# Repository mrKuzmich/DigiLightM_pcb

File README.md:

# DigiLight-M
DigiLight-M is a project of digital light organ with automat of light effects. This project based on [DigiLight](https://cxem.net/sound/light/light127.php) project of user [AVR](https://cxem.net/profile/17379).

This part of the project contains the schematic of the device itself and PCB. The source codes of the ATMega32 microcontroller firmware in the C language you can see in another part of the project [DigiLightM_firmware](https://github.com/mrKuzmich/DigiLightM_firmware).

## Whats new
1. Changed the power suply of the digital and analog parts of circuit;
2. Added line-in and microphone input with electronic source selection;
3. SD Card adapter replaced with direct connection of MicroSD Card;
4. Redesigned PCB. 

## Appearance

## Schematic

## Firmware
[DigiLightM_firmware](https://github.com/mrKuzmich/DigiLightM_firmware) repository.

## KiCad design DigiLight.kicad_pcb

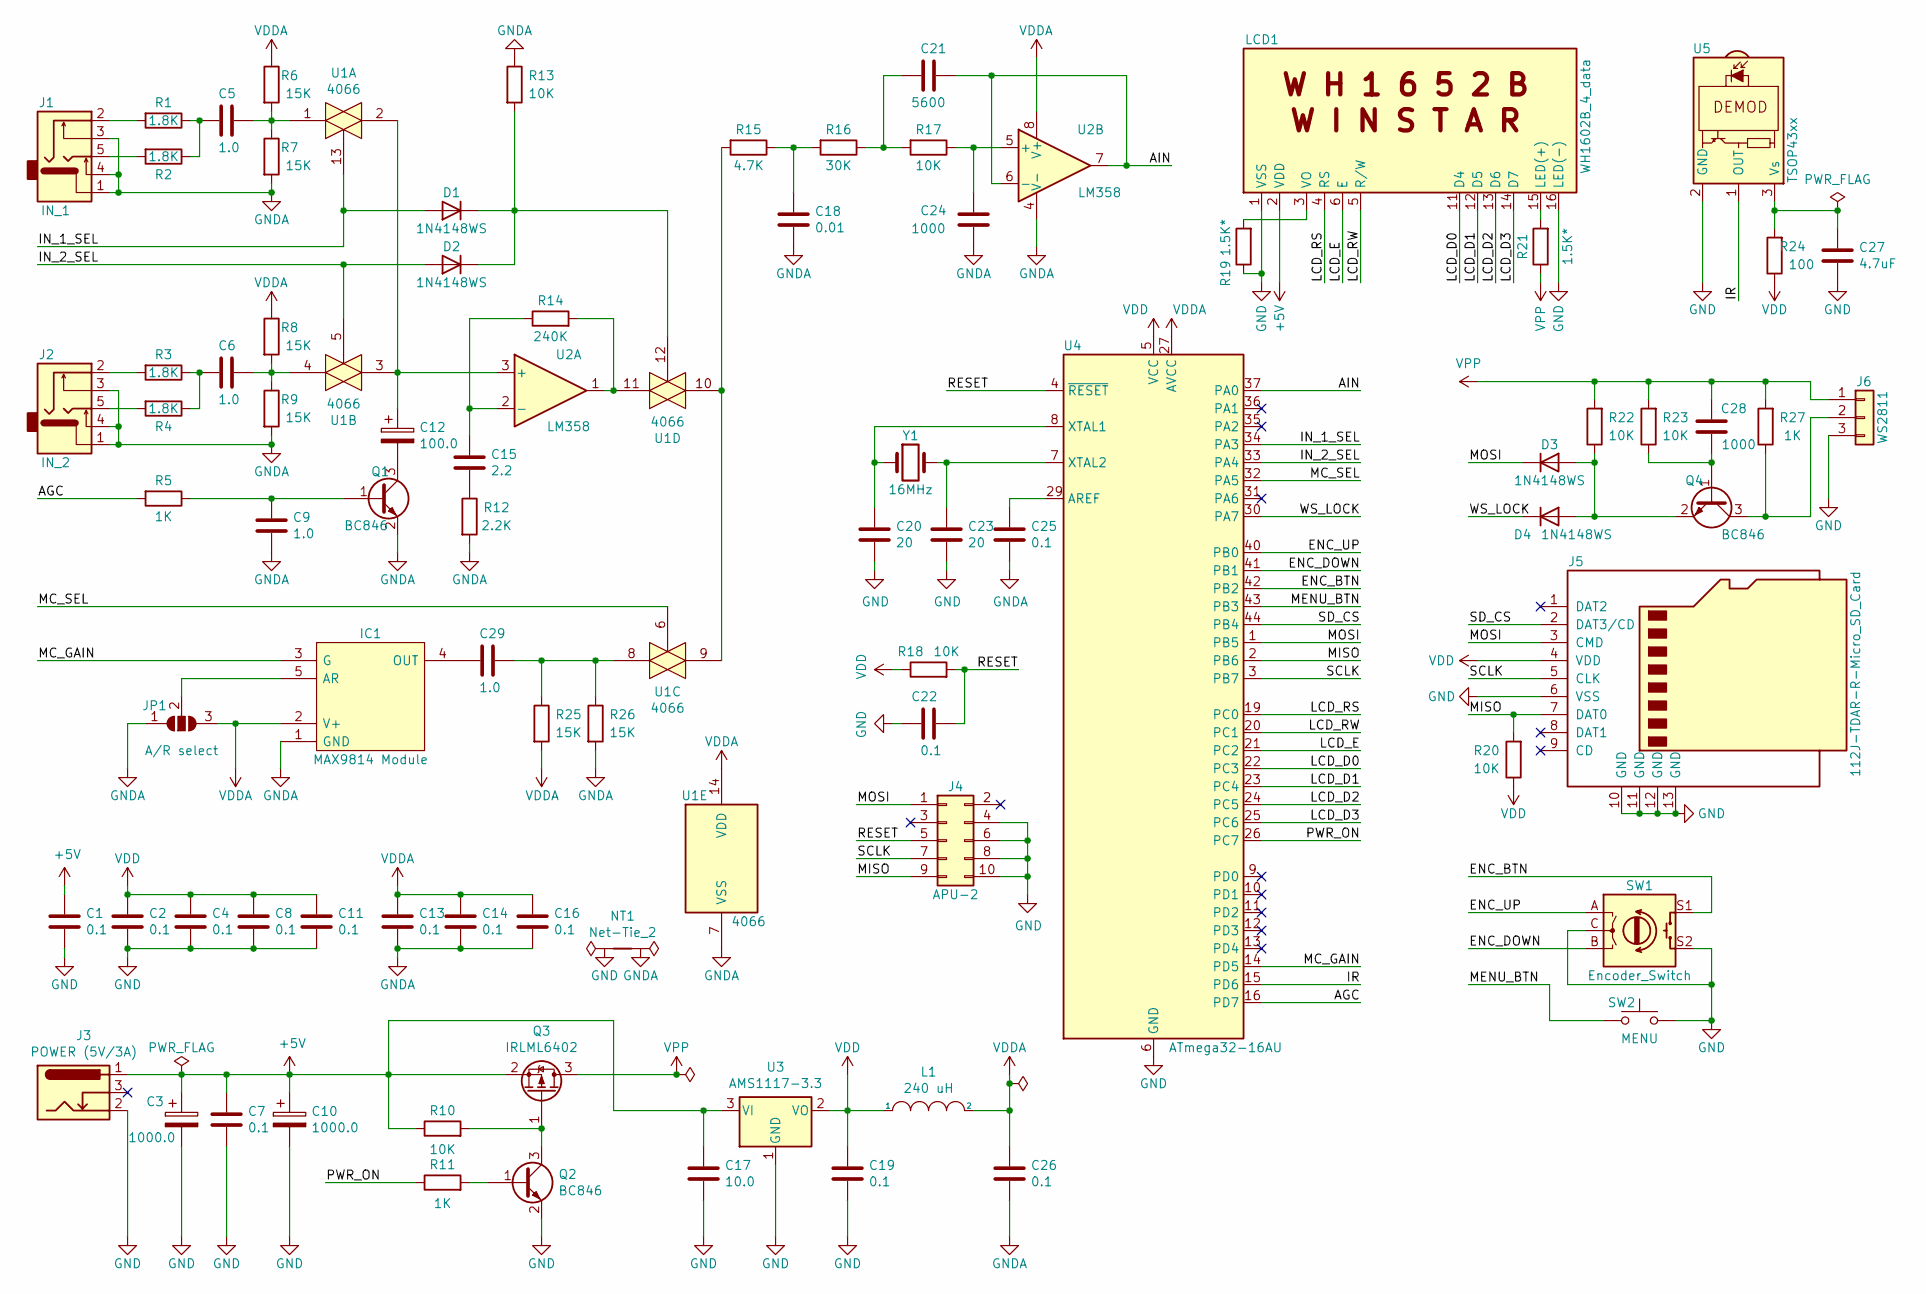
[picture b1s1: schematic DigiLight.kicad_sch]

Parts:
C1, C2, C4, C7, C8, C11, C13, C14, C16, C19, C22, C25, C26: 0.1; C_1206_3216Metric
C3, C10: 1000.0; CP_Radial_D8.0mm_P5.00mm
C5, C6, C9, C29: 1.0; C_1206_3216Metric
C12: 100.0; CP_EIA-3528-21_Kemet-B_Pad1.50x2.35mm_HandSolder
C15: 2.2; C_1206_3216Metric
C17: 10.0; C_1206_3216Metric
C18: 0.01; C_1206_3216Metric
C20, C23: 20; C_1206_3216Metric
C21: 5600; C_1206_3216Metric
C24, C28: 1000; C_1206_3216Metric
C27: 4.7uF; C_1206_3216Metric
D1, D2, D3, D4: 1N4148WS; D_SOD-323
IC1: MAX9814 Module; 1713; Manufacturer_Part_Number 1713; Mouser Part Number 485-1713
J1: IN_1; PJ-307
J2: IN_2; PJ-307
J3: POWER (5V/3A); DC-044
J4: APU-2; PinSocket_2x05_P2.54mm_Vertical
J5: 112J-TDAR-R-Micro_SD_Card; 112JTDARR
J6: WS2811; JST_EH_S3B-EH_1x03_P2.50mm_Horizontal
JP1: A/R select; SolderJumper-3_P1.3mm_Open_RoundedPad1.0x1.5mm
L1: 240 uH; L_1210_3225Metric
LCD1: WH1602B_4_data; WC1602A_4_data
NT1: Net-Tie_2; NetTie-2_SMD_Pad2.0mm
Q1, Q2, Q4: BC846; SOT-23
Q3: IRLML6402; SOT-23
R1, R2, R3, R4: 1.8K; R_1206_3216Metric
R5, R11, R27: 1K; R_1206_3216Metric
R6, R7, R8, R9, R25, R26: 15K; R_1206_3216Metric
R10, R13, R17, R18, R20, R22, R23: 10K; R_1206_3216Metric
R12: 2.2K; R_1206_3216Metric
R14: 240K; R_1206_3216Metric
R15: 4.7K; R_1206_3216Metric
R16: 30K; R_1206_3216Metric
R19, R21: 1.5K*; R_1206_3216Metric
R24: 100; R_1206_3216Metric
SW1: Encoder_Switch; PEC11R4220FS0024
SW2: MENU; SW_PUSH_6mm_H13mm
U1: 4066; SOIC-14_3.9x8.7mm_P1.27mm
U2: LM358; SOIC-8_3.9x4.9mm_P1.27mm
U3: AMS1117-3.3; SOT-223-3_TabPin2
U4: ATmega32-16AU; TQFP-44_10x10mm_P0.8mm
U5: TSOP43xx; Vishay_MOLD-3Pin
Y1: 16MHz; Crystal_HC49-4H_Vertical

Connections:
+5V: C1.1, C3.1, C7.1, C10.1, C17.1, J3.1, LCD1.2 (VDD), Q3.2 (S), R10.1, U3.3 (VI)
/AGC: R5.2, U4.16 (PD7)
/AIN: C21.1, U2.6 (-), U2.7, U4.37 (PA0)
/ENC_BTN: SW1.S1, U4.42 (PB2)
/ENC_DOWN: SW1.B, U4.41 (PB1)
/ENC_UP: SW1.A, U4.40 (PB0)
/IN_1_SEL: D1.2 (A), U1.13, U4.34 (PA3)
/IN_2_SEL: D2.2 (A), U1.5, U4.33 (PA4)
/IR: U4.15 (PD6), U5.1 (OUT)
/LCD_D0: LCD1.11 (D4), U4.22 (PC3)
/LCD_D1: LCD1.12 (D5), U4.23 (PC4)
/LCD_D2: LCD1.13 (D6), U4.24 (PC5)
/LCD_D3: LCD1.14 (D7), U4.25 (PC6)
/LCD_E: LCD1.6 (E), U4.21 (PC2)
/LCD_RS: LCD1.4 (RS), U4.19 (PC0)
/LCD_RW: LCD1.5 (R/W), U4.20 (PC1)
/MC_GAIN: IC1.3 (G), U4.14 (PD5)
/MC_SEL: U1.6, U4.32 (PA5)
/MENU_BTN: SW2.1, U4.43 (PB3)
/MISO: J4.9, J5.7 (DAT0), R20.2, U4.2 (PB6)
/MOSI: D3.1 (K), J4.1, J5.3 (CMD), U4.1 (PB5)
/PWR_ON: R11.1, U4.26 (PC7)
/RESET: C22.1, J4.5, R18.2, U4.4 (~RESET)
/SCLK: J4.7, J5.5 (CLK), U4.3 (PB7)
/SD_CS: J5.2 (DAT3/CD), U4.44 (PB4)
/WS_LOCK: D4.1 (K), U4.30 (PA7)
GND: C1.2, C2.2, C3.2, C4.2, C7.2, C8.2, C10.2, C11.2, C17.2, C19.2, C20.2, C22.2, C23.2, C27.2, J3.2, J4.4, J4.6, J4.8, J4.10, J5.6 (VSS), J5.10 (GND), J5.11 (GND), J5.12 (GND), J5.13 (GND), J6.3, LCD1.1 (VSS), LCD1.16 (LED(-)), NT1.1, Q2.2 (E), R19.1, SW1.C, SW1.S2, SW2.2, U3.1 (GND), U4.6 (GND), U4.18 (GND), U4.28 (GND), U4.39 (GND), U5.2 (GND)
GNDA: C9.2, C13.2, C14.2, C16.2, C18.2, C24.2, C25.2, C26.2, IC1.1 (GND), J1.1, J1.3, J1.4, J2.1, J2.3, J2.4, JP1.1 (A), NT1.2, Q1.2 (E), R7.2, R9.2, R12.2, R13.1, R26.2, U1.7 (VSS), U2.4 (V-)
unnamed: C5.1, R6.2, R7.1, U1.1
unnamed: C5.2, R1.1, R2.1
unnamed: C6.1, R8.2, R9.1, U1.4
unnamed: C6.2, R3.1, R4.1
unnamed: C9.1, Q1.1 (B), R5.1
unnamed: C12.1, U1.2, U1.3, U2.3 (+)
unnamed: C12.2, Q1.3 (C)
unnamed: C15.1, R14.1, U2.2 (-)
unnamed: C15.2, R12.1
unnamed: C18.1, R15.1, R16.2
unnamed: C20.1, U4.8 (XTAL1), Y1.1
unnamed: C21.2, R16.1, R17.2
unnamed: C23.1, U4.7 (XTAL2), Y1.2
unnamed: C24.1, R17.1, U2.5 (+)
unnamed: C25.1, U4.29 (AREF)
unnamed: C27.1, R24.2, U5.3 (Vs)
unnamed: C28.1, Q4.1 (B), R23.1
unnamed: C29.1, R25.1, R26.1, U1.8
unnamed: C29.2, IC1.4 (OUT)
unnamed: D1.1 (K), D2.1 (K), R13.2, U1.12
unnamed: D3.2 (A), D4.2 (A), Q4.2 (E), R22.1
unnamed: IC1.5 (AR), JP1.2 (C)
unnamed: J1.2, R1.2
unnamed: J1.5, R2.2
unnamed: J2.2, R3.2
unnamed: J2.5, R4.2
unnamed: J6.2, Q4.3 (C), R27.1
unnamed: LCD1.3 (VO), R19.2
unnamed: LCD1.15 (LED(+)), R21.2
unnamed: Q2.1 (B), R11.2
unnamed: Q2.3 (C), Q3.1 (G), R10.2
unnamed: R14.2, U1.11, U2.1
unnamed: R15.2, U1.9, U1.10
VDD: C2.1, C4.1, C8.1, C11.1, C19.1, J5.4 (VDD), L1.1, R18.1, R20.1, R24.1, U3.2 (VO), U4.5 (VCC), U4.17 (VCC), U4.38 (VCC)
VDDA: C13.1, C14.1, C16.1, C26.1, IC1.2 (V+), JP1.3 (B), L1.2, R6.1, R8.1, R25.2, U1.14 (VDD), U2.8 (V+), U4.27 (AVCC)
VPP: C28.2, J6.1, Q3.3 (D), R21.1, R22.2, R23.2, R27.2

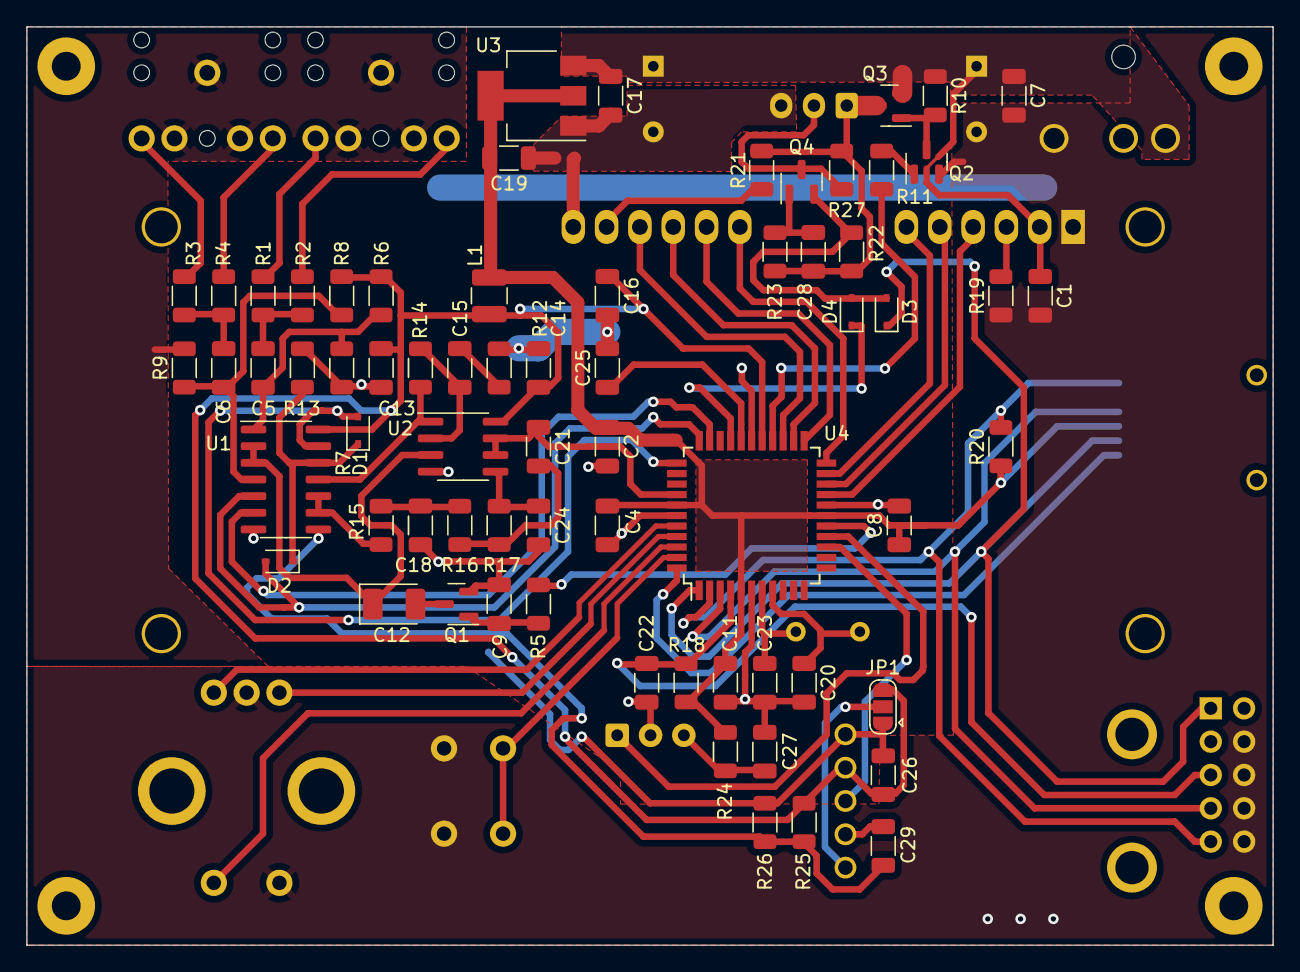
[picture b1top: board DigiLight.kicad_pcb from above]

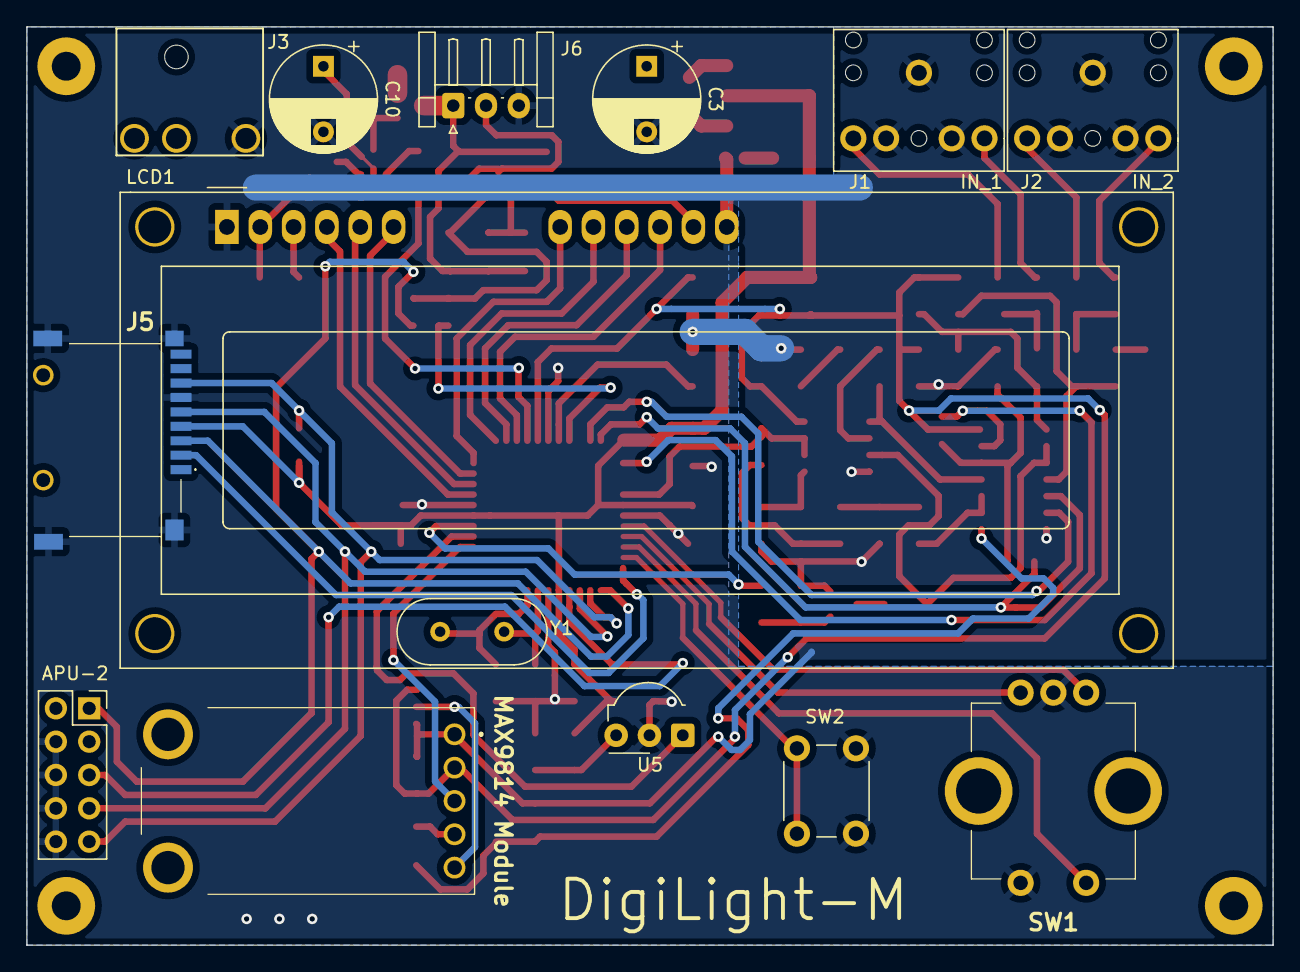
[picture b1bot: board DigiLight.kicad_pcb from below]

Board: 2 copper layers, 95.0 x 70.0 mm, 83 parts (15 on the bottom side), 64 nets.

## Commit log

2020-03-19 Init commit. Circuit of DigiLight with two lines inputs and microphone input.
2020-03-23 Add .gitignore
2020-03-23 Add Ampifer cirquit test project
2020-03-23 Refactoring input circuit, reassigned MC pins, replace LCD footprint, create PCB template
2020-04-08 Tracing PCB finished
2020-04-19 Final trace
2020-04-19 Recalculated 3rd order Sallen-Key Low-pass filter
2020-11-13 Adding mofels of dc-044 connector and wc1602 display
2020-11-13 Update models, pcb build finish, change output key.
2020-11-13 Modify .gitignore
2020-11-16 Added Proteus model of output key
2020-11-16 Changed C28 capcity
2020-11-16 Changed footprint of microphone module, added bias voltage to microphone signal, changed power suply of LCD.
2020-11-16 Refactoring
2021-02-15 Changed output switch on schematic and pcb
2021-02-15 Added 'out' directory with output files
2021-02-15 Changed scheme.png resolution
2021-02-15 Update README.md
    Add schematic
2021-02-15 Added appearance.png
2021-02-15 Update README.md
    Adding appearance.png
2021-02-26 Update README.md
    Added clarifications
2021-11-02 scheme.svg
2021-11-02 Changed the contour of the PCB
2022-10-03 DigiLight-backups directotry added to .gitignore
2022-10-12 Migrating to Kicad 6.0. Removed external links.
2022-10-20 Maked production version of PCB
2022-11-01 Small cosmetic edits. Production gerber files.
2022-11-02 Power connector replaced to USB type-c
